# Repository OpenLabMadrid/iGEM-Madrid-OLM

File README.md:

# iGEM-Madrid-OLM
Here you will find all the codes & sketches that the Madrid-OLM team has developed for iGEM2018

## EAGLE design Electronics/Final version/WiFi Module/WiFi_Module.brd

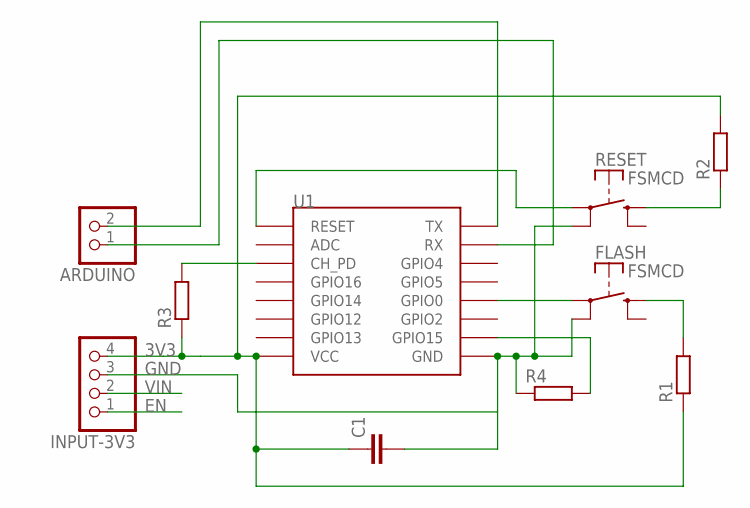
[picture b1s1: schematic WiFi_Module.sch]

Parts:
ARDUINO: PINHD-1X2; 1X02
C1: C2.5/2; C2.5-2
FLASH: FSMCD
INPUT-3V3: PINHD-1X4; 1X04
R1, R2, R3, R4: R-EU_0204/5; 0204/5
RESET: FSMCD
U1: ESP12SMD; ESP12-SMD

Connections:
3V3: C1.1, INPUT-3V3.4, R1.1, R2.2, R3.1, U1.VCC
EN: INPUT-3V3.1
GND: C1.2, FLASH.P$2, INPUT-3V3.3, R4.1, RESET.P$2, U1.GND
unnamed: R2.1, RESET.P$3 (S)
unnamed: RESET.P$1, U1.RESET
unnamed: FLASH.P$1, U1.GPIO0
unnamed: FLASH.P$3 (S), R1.2
unnamed: R3.2, U1.CH_PD
unnamed: R4.2, U1.GPIO15
unnamed: ARDUINO.2, U1.TXD0 (TX)
unnamed: ARDUINO.1, U1.RXD0 (RX)
VIN: INPUT-3V3.2

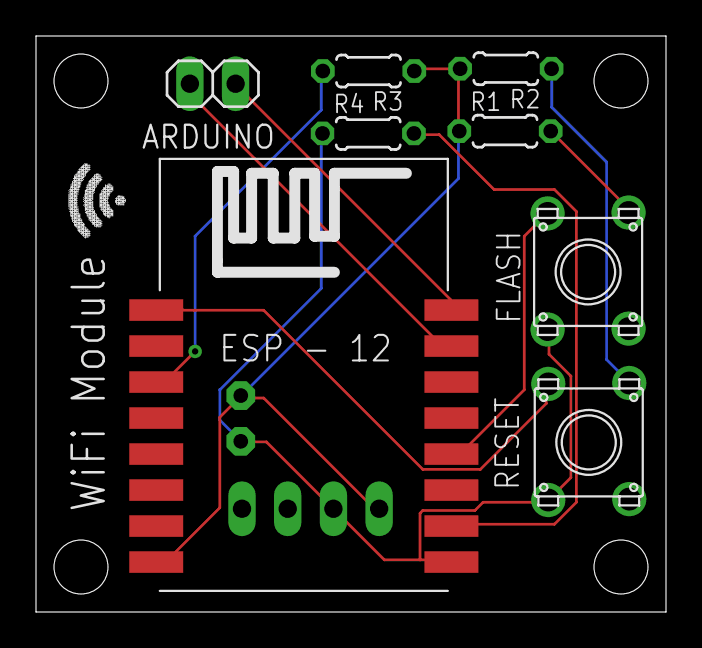
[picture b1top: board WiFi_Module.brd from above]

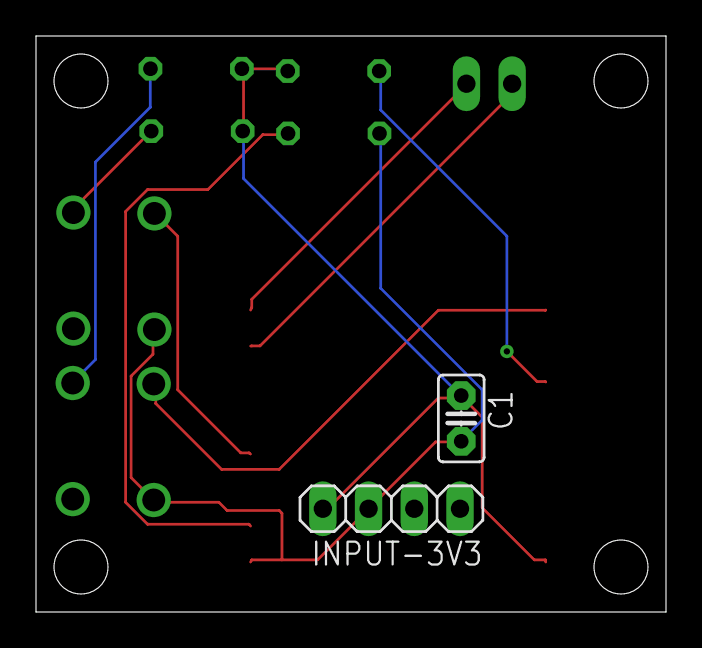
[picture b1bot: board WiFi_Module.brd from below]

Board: 2 copper layers, 35.0 x 32.0 mm, 10 parts (2 on the bottom side), 10 nets.

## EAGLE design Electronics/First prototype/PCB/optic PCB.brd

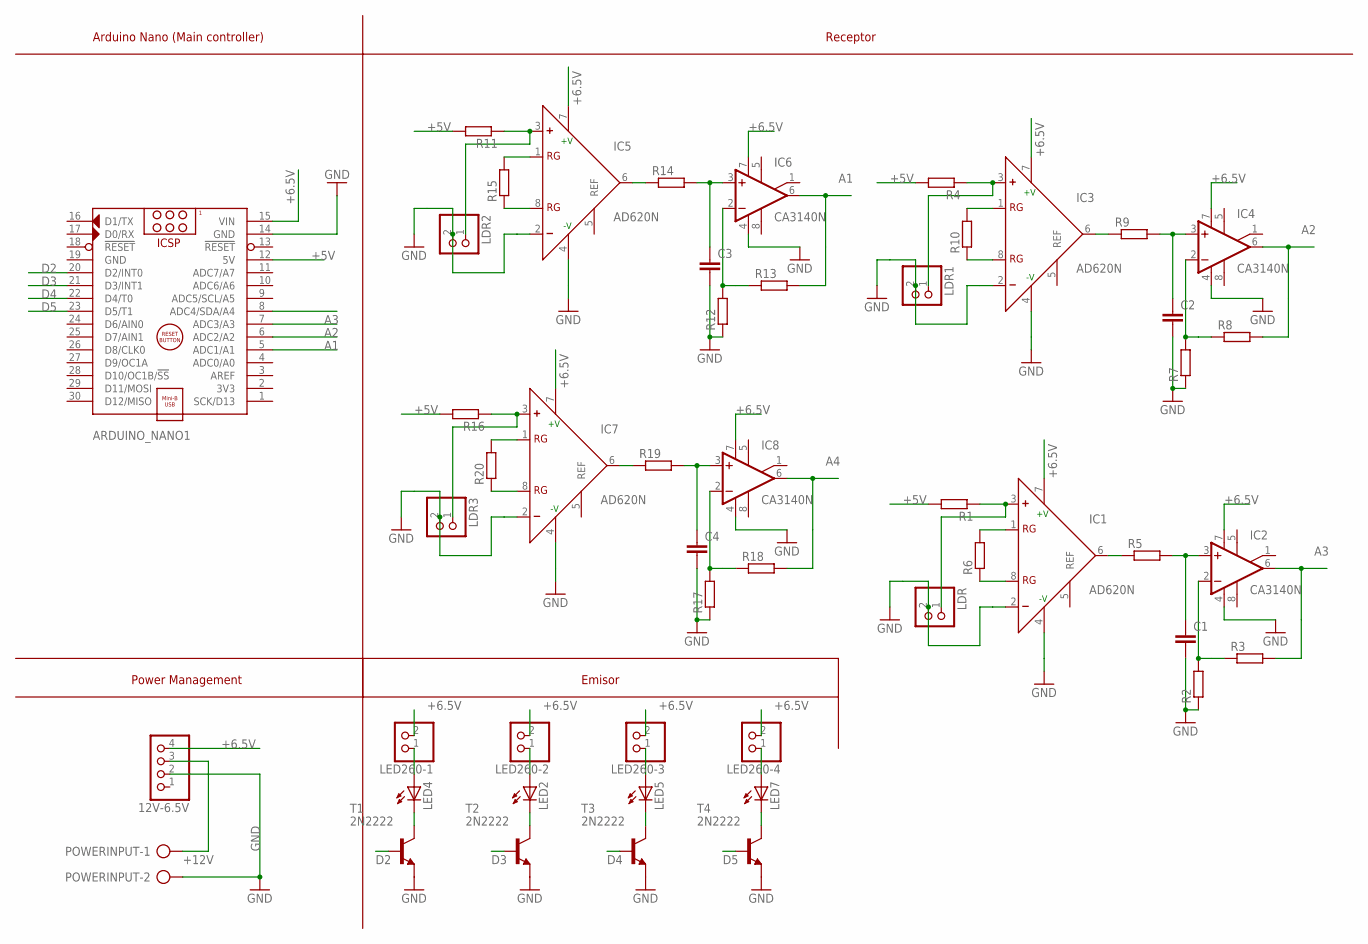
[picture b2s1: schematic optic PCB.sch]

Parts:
12V-6.5V: PINHD-1X4; 1X04
ARDUINO_NANO1: ARDUINO_NANO
C1, C2, C3, C4: C2.5/2; C2.5-2
IC1, IC3, IC5, IC7: AD620N; DIL08
IC2, IC4, IC6, IC8: CA3140N; DIL08
LDR, LDR1, LDR2, LDR3: PINHD-1X2; 1X02
LED2, LED4, LED5, LED7: LED5MM
LED260-1, LED260-2, LED260-3, LED260-4: PINHD-1X2; 1X02
POWERINPUT: AK500/2
R1, R2, R3, R4, R5, R6, R7, R8, R9, R10, R11, R12, R13, R14, R15, R16, R17, R18, R19, R20: R-EU_0204/5; 0204/5
T1, T2, T3, T4: 2N2222; TO18

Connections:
+5V: ARDUINO_NANO1.12 (5V), R1.2, R4.2, R11.2, R16.2
+6.5V: 12V-6.5V.4, ARDUINO_NANO1.15 (VIN), IC1.7 (+V), IC2.7 (V+), IC3.7 (+V), IC4.7 (V+), IC5.7 (+V), IC6.7 (V+), IC7.7 (+V), IC8.7 (V+), LED260-1.2, LED260-2.2, LED260-3.2, LED260-4.2
+12V: 12V-6.5V.3, POWERINPUT.1
A1: ARDUINO_NANO1.5 (ADC1/A1), IC6.6 (OUT), R13.2
A2: ARDUINO_NANO1.6 (ADC2/A2), IC4.6 (OUT), R8.2
A3: ARDUINO_NANO1.7 (ADC3/A3), IC2.6 (OUT), R3.2
A4: ARDUINO_NANO1.8 (ADC4/SDA/A4), IC8.6 (OUT), R18.2
D2: ARDUINO_NANO1.20 (D2/INT0), T1.2 (B)
D3: ARDUINO_NANO1.21 (D3/INT1), T2.2 (B)
D4: ARDUINO_NANO1.22 (D4/T0), T3.2 (B)
D5: ARDUINO_NANO1.23 (D5/T1), T4.2 (B)
GND: 12V-6.5V.2, ARDUINO_NANO1.14 (GND), ARDUINO_NANO1.19 (GND), C1.2, C2.2, C3.2, C4.2, IC1.2 (-), IC1.4 (-V), IC2.4 (V-), IC3.2 (-), IC3.4 (-V), IC4.4 (V-), IC5.2 (-), IC5.4 (-V), IC6.4 (V-), IC7.2 (-), IC7.4 (-V), IC8.4 (V-), LDR.2, LDR1.2, LDR2.2, LDR3.2, POWERINPUT.2, R2.1, R7.1, R12.1, R17.1, T1.1 (E), T2.1 (E), T3.1 (E), T4.1 (E)
unnamed: IC3.1 (RG), R10.2
unnamed: IC1.1 (RG), R6.2
unnamed: IC1.8 (RG), R6.1
unnamed: IC3.8 (RG), R10.1
unnamed: IC1.6 (OUT), R5.1
unnamed: C1.1, IC2.3 (+IN), R5.2
unnamed: IC2.2 (-IN), R2.2, R3.1
unnamed: LED4.K (C), T1.3 (C)
unnamed: IC1.3 (+), LDR.1, R1.1
unnamed: IC3.6 (OUT), R9.1
unnamed: C2.1, IC4.3 (+IN), R9.2
unnamed: IC4.2 (-IN), R7.2, R8.1
unnamed: IC3.3 (+), LDR1.1, R4.1
unnamed: IC5.1 (RG), R15.2
unnamed: IC5.8 (RG), R15.1
unnamed: IC5.6 (OUT), R14.1
unnamed: C3.1, IC6.3 (+IN), R14.2
unnamed: IC6.2 (-IN), R12.2, R13.1
unnamed: IC5.3 (+), LDR2.1, R11.1
unnamed: IC7.1 (RG), R20.2
unnamed: IC7.8 (RG), R20.1
unnamed: IC7.6 (OUT), R19.1
unnamed: C4.1, IC8.3 (+IN), R19.2
unnamed: IC8.2 (-IN), R17.2, R18.1
unnamed: IC7.3 (+), LDR3.1, R16.1
unnamed: LED4.A, LED260-1.1
unnamed: LED2.K (C), T2.3 (C)
unnamed: LED2.A, LED260-2.1
unnamed: LED5.K (C), T3.3 (C)
unnamed: LED5.A, LED260-3.1
unnamed: LED7.K (C), T4.3 (C)
unnamed: LED7.A, LED260-4.1

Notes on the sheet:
Power Management
Arduino Nano (Main controller)
Receptor
Emisor

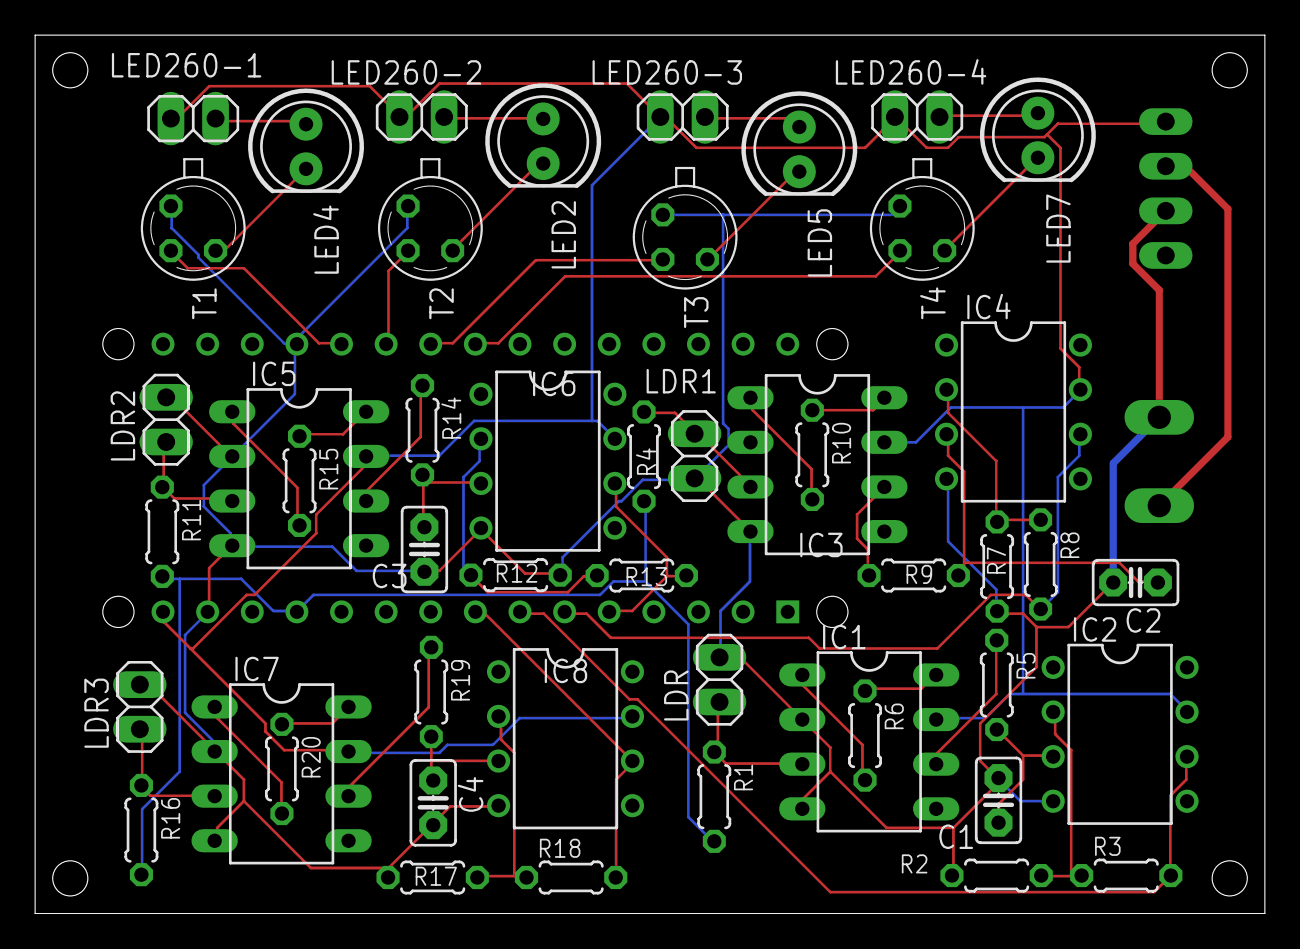
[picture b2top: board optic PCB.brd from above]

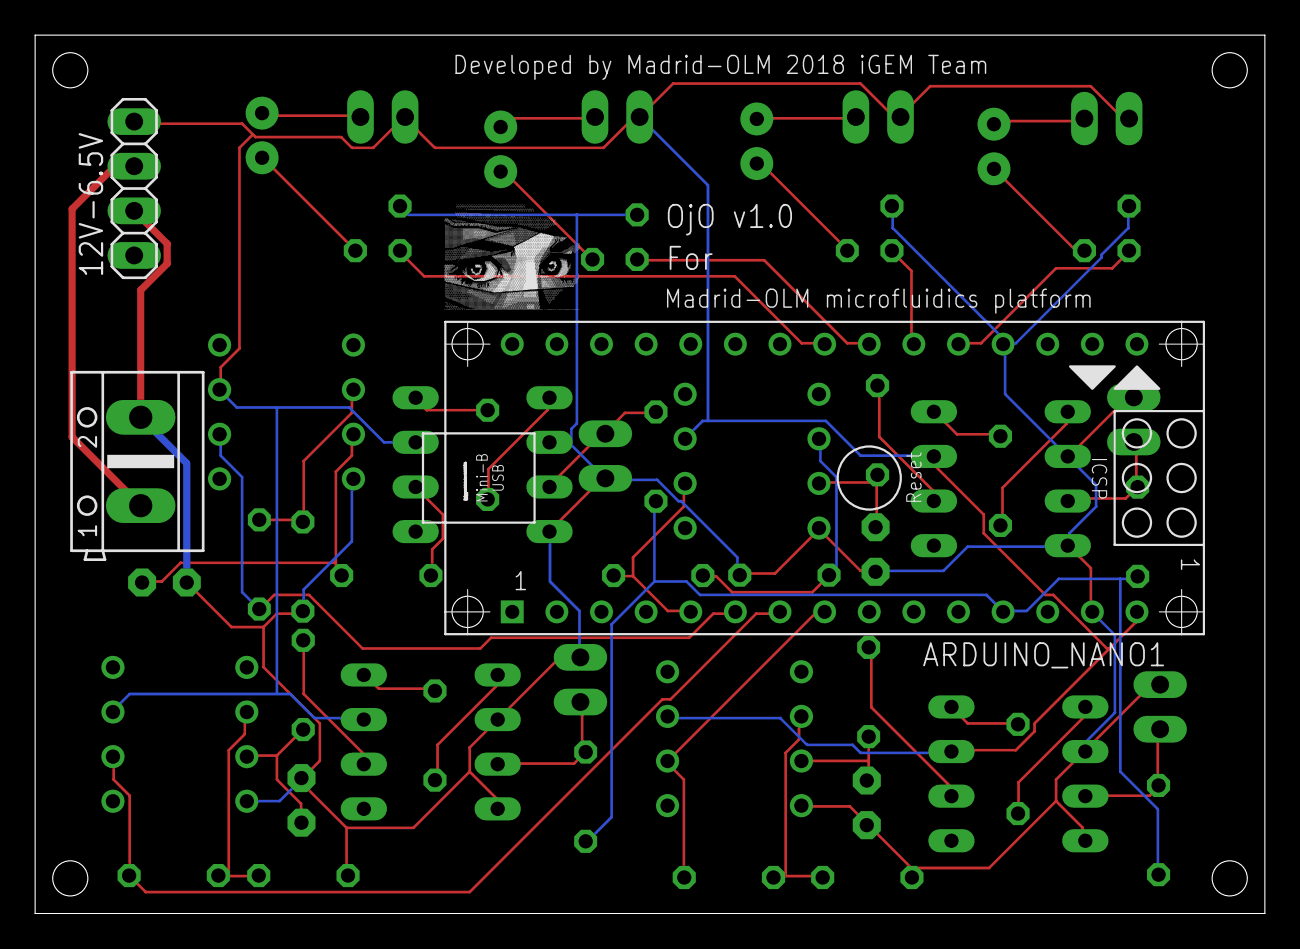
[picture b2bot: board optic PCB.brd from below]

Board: 2 copper layers, 70.0 x 50.0 mm, 51 parts (3 on the bottom side), 44 nets.

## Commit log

2018-09-30 Upload of Arduino code
2018-10-03 Mixer+electrode chip
    adding the first microfluidic chip to the repository
2018-10-04 adfasf
2018-10-04 adsfd
2018-10-04 flow studies
2018-10-04 All modules-all together
2018-10-04 libraries
2018-10-04 .stl files with 0.7mm needle input
2018-10-04 Create Laser Engraver Software
2018-10-04 Laser Engraver Software
2018-10-04 Required software for Laser Hacking
2018-10-04 droplets design
2018-10-05 Final configure of Inkscape with the extension
2018-10-05 asdad
2018-10-05 final inkscape configuration
2018-10-05 ahora si coñooo
2018-10-05 vamos vamosss
2018-10-05 asfds
2018-10-05 ffyjnjljhln
2018-10-05 Microfluidic Chips (.dxf .ipt .dwg)
2018-10-05 zsdfsf
2018-10-07 First prototype files
2018-10-07 PC code finished + Arduino libraries upload
2018-10-08 Microfluidic designs
2018-10-08 afafs
2018-10-08 extract UniversalGcode sender
    Updates
2018-10-09 Update CAD/Pressure pump/Laser cut .dxf files/OldVersions/Transparent_3mm_800x500.0001.dwg
    a
2018-10-09 asdfsadf
2018-10-10 Laser files ready to cut
2018-10-10 Exploded view
2018-10-10 nitrocellulose stl upload
2018-10-10 eliminar mierda
2018-10-11 Updating
2018-10-13 New update
2018-10-13 cleaning
2018-10-14 WiFi module upload
2018-10-14 modules
2018-10-14 optic PCB

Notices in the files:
parts and their libraries:
SparkFun: Licensing: CC v3.0 Share-Alike You are welcome to use this library for commercial purposes.
